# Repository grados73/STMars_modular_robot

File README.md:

# STMars Modular Robot
>My version of popular SMARS project, but THIS is distinguished by the fact that it is on STM32F411.

## Table of contents
* [General info](#general-info)
* [Screenshots](#screenshots)
* [Technologies](#technologies)
* [Features](#features)
* [Status](#status)
* [Inspiration](#inspiration)
* [Contact](#contact)

## General info
It is educational SMARS project based on STM32 BlackPill. I created this project to learn how to develop projects on STM32 and how to use my own 3D Printer.

STMars has two modes of working, the first one is remote control via Bluetooth, using a phone and HC-05 module, second mode is the ability to drive autonomously and to avoid obstacles.

## Screenshots

## Technologies
C,
HAL for STM32F4
Low-Layer drivers

STM32CubeIDE,
RoboRemo

## Code Examples

## Features
UART in DMA mode,
State machine.

## To-do list
Upgrade standalone mode.
Add calibration of engine speed by optocoupler

## Status
Project is in progress and i will develop them to learn ARM and STM32.

## Inspiration
It will be added.

## Contact
Created by https://www.linkedin.com/in/kamil-gradowski-8706991aa - feel free to contact me!
grados73

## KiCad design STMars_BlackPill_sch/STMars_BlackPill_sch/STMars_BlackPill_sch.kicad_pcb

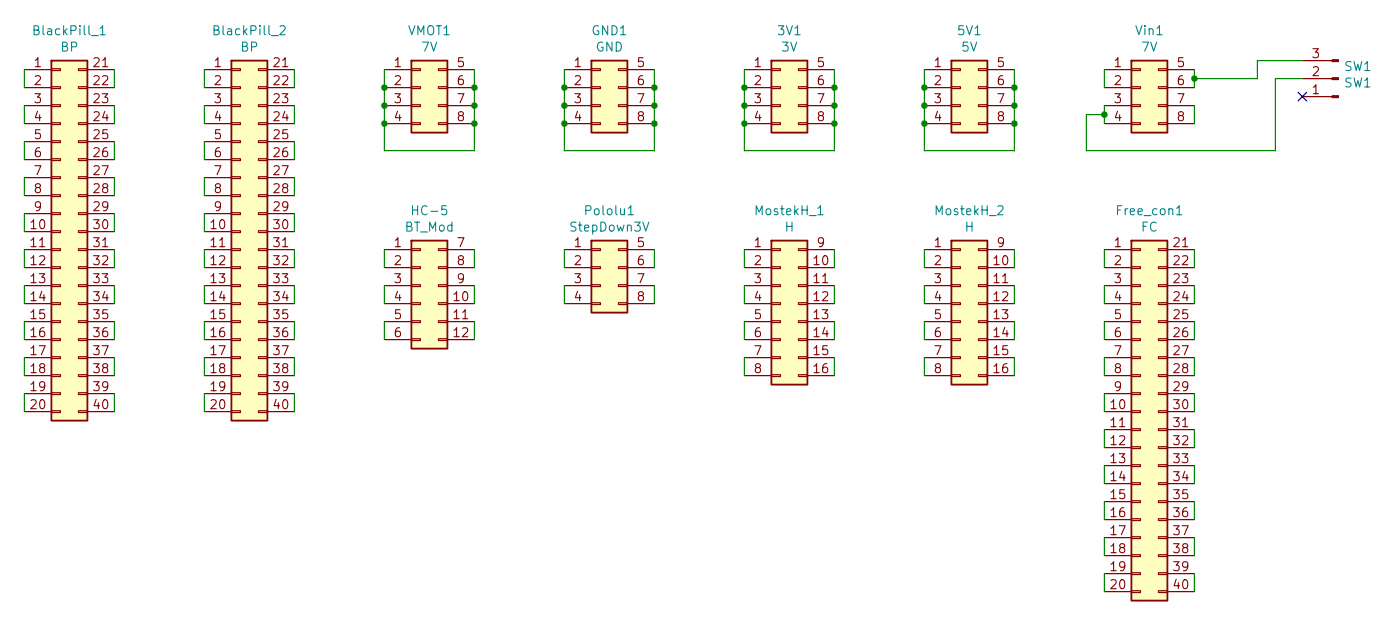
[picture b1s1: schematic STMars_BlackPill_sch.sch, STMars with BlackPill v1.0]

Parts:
3V1: 3V; PinHeader_2x04_P2.54mm_Vertical
5V1: 5V; PinHeader_2x04_P2.54mm_Vertical
BlackPill_1, BlackPill_2: BP; PinHeader_2x20_P2.54mm_Vertical
Free_con1: FC; PinHeader_2x20_P2.54mm_Vertical
GND1: GND; PinHeader_2x04_P2.54mm_Vertical
HC-5: BT_Mod; PinHeader_2x06_P2.54mm_Vertical
MostekH_1, MostekH_2: H; PinHeader_2x08_P2.54mm_Vertical
Pololu1: StepDown3V; PinHeader_2x04_P2.54mm_Vertical
SW1: SW1; PinHeader_1x03_P2.54mm_Vertical
VMOT1: 7V; PinHeader_2x04_P2.54mm_Vertical
Vin1: 7V; PinHeader_2x04_P2.54mm_Vertical

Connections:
unnamed: 3V1.1, 3V1.2, 3V1.3, 3V1.4, 3V1.5, 3V1.6, 3V1.7, 3V1.8
unnamed: 5V1.1, 5V1.2, 5V1.3, 5V1.4, 5V1.5, 5V1.6, 5V1.7, 5V1.8
unnamed: BlackPill_1.1, BlackPill_1.2
unnamed: BlackPill_1.3, BlackPill_1.4
unnamed: BlackPill_1.5, BlackPill_1.6
unnamed: BlackPill_1.7, BlackPill_1.8
unnamed: BlackPill_1.9, BlackPill_1.10
unnamed: BlackPill_1.11, BlackPill_1.12
unnamed: BlackPill_1.13, BlackPill_1.14
unnamed: BlackPill_1.15, BlackPill_1.16
unnamed: BlackPill_1.17, BlackPill_1.18
unnamed: BlackPill_1.19, BlackPill_1.20
unnamed: BlackPill_1.21, BlackPill_1.22
unnamed: BlackPill_1.23, BlackPill_1.24
unnamed: BlackPill_1.25, BlackPill_1.26
unnamed: BlackPill_1.27, BlackPill_1.28
unnamed: BlackPill_1.29, BlackPill_1.30
unnamed: BlackPill_1.31, BlackPill_1.32
unnamed: BlackPill_1.33, BlackPill_1.34
unnamed: BlackPill_1.35, BlackPill_1.36
unnamed: BlackPill_1.37, BlackPill_1.38
unnamed: BlackPill_1.39, BlackPill_1.40
unnamed: BlackPill_2.1, BlackPill_2.2
unnamed: BlackPill_2.3, BlackPill_2.4
unnamed: BlackPill_2.5, BlackPill_2.6
unnamed: BlackPill_2.7, BlackPill_2.8
unnamed: BlackPill_2.9, BlackPill_2.10
unnamed: BlackPill_2.11, BlackPill_2.12
unnamed: BlackPill_2.13, BlackPill_2.14
unnamed: BlackPill_2.15, BlackPill_2.16
unnamed: BlackPill_2.17, BlackPill_2.18
unnamed: BlackPill_2.19, BlackPill_2.20
unnamed: BlackPill_2.21, BlackPill_2.22
unnamed: BlackPill_2.23, BlackPill_2.24
unnamed: BlackPill_2.25, BlackPill_2.26
unnamed: BlackPill_2.27, BlackPill_2.28
unnamed: BlackPill_2.29, BlackPill_2.30
unnamed: BlackPill_2.31, BlackPill_2.32
unnamed: BlackPill_2.33, BlackPill_2.34
unnamed: BlackPill_2.35, BlackPill_2.36
unnamed: BlackPill_2.37, BlackPill_2.38
unnamed: BlackPill_2.39, BlackPill_2.40
unnamed: Free_con1.1, Free_con1.2
unnamed: Free_con1.3, Free_con1.4
unnamed: Free_con1.5, Free_con1.6
unnamed: Free_con1.7, Free_con1.8
unnamed: Free_con1.9, Free_con1.10
unnamed: Free_con1.11, Free_con1.12
unnamed: Free_con1.13, Free_con1.14
unnamed: Free_con1.15, Free_con1.16
unnamed: Free_con1.17, Free_con1.18
unnamed: Free_con1.19, Free_con1.20
unnamed: Free_con1.21, Free_con1.22
unnamed: Free_con1.23, Free_con1.24
unnamed: Free_con1.25, Free_con1.26
unnamed: Free_con1.27, Free_con1.28
unnamed: Free_con1.29, Free_con1.30
unnamed: Free_con1.31, Free_con1.32
unnamed: Free_con1.33, Free_con1.34
unnamed: Free_con1.35, Free_con1.36
unnamed: Free_con1.37, Free_con1.38
unnamed: Free_con1.39, Free_con1.40
unnamed: GND1.1, GND1.2, GND1.3, GND1.4, GND1.5, GND1.6, GND1.7, GND1.8
unnamed: HC-5.1, HC-5.2
unnamed: HC-5.3, HC-5.4
unnamed: HC-5.5, HC-5.6
unnamed: HC-5.7, HC-5.8
unnamed: HC-5.9, HC-5.10
unnamed: HC-5.11, HC-5.12
unnamed: MostekH_1.1, MostekH_1.2
unnamed: MostekH_1.3, MostekH_1.4
unnamed: MostekH_1.5, MostekH_1.6
unnamed: MostekH_1.7, MostekH_1.8
unnamed: MostekH_1.9, MostekH_1.10
unnamed: MostekH_1.11, MostekH_1.12
unnamed: MostekH_1.13, MostekH_1.14
unnamed: MostekH_1.15, MostekH_1.16
unnamed: MostekH_2.1, MostekH_2.2
unnamed: MostekH_2.3, MostekH_2.4
unnamed: MostekH_2.5, MostekH_2.6
unnamed: MostekH_2.7, MostekH_2.8
unnamed: MostekH_2.9, MostekH_2.10
unnamed: MostekH_2.11, MostekH_2.12
unnamed: MostekH_2.13, MostekH_2.14
unnamed: MostekH_2.15, MostekH_2.16
unnamed: Pololu1.1, Pololu1.2
unnamed: Pololu1.3, Pololu1.4
unnamed: Pololu1.5, Pololu1.6
unnamed: Pololu1.7, Pololu1.8
unnamed: SW1.2, Vin1.3, Vin1.4
unnamed: SW1.3, Vin1.5, Vin1.6
unnamed: VMOT1.1, VMOT1.2, VMOT1.3, VMOT1.4, VMOT1.5, VMOT1.6, VMOT1.7, VMOT1.8
unnamed: Vin1.1, Vin1.2
unnamed: Vin1.7, Vin1.8

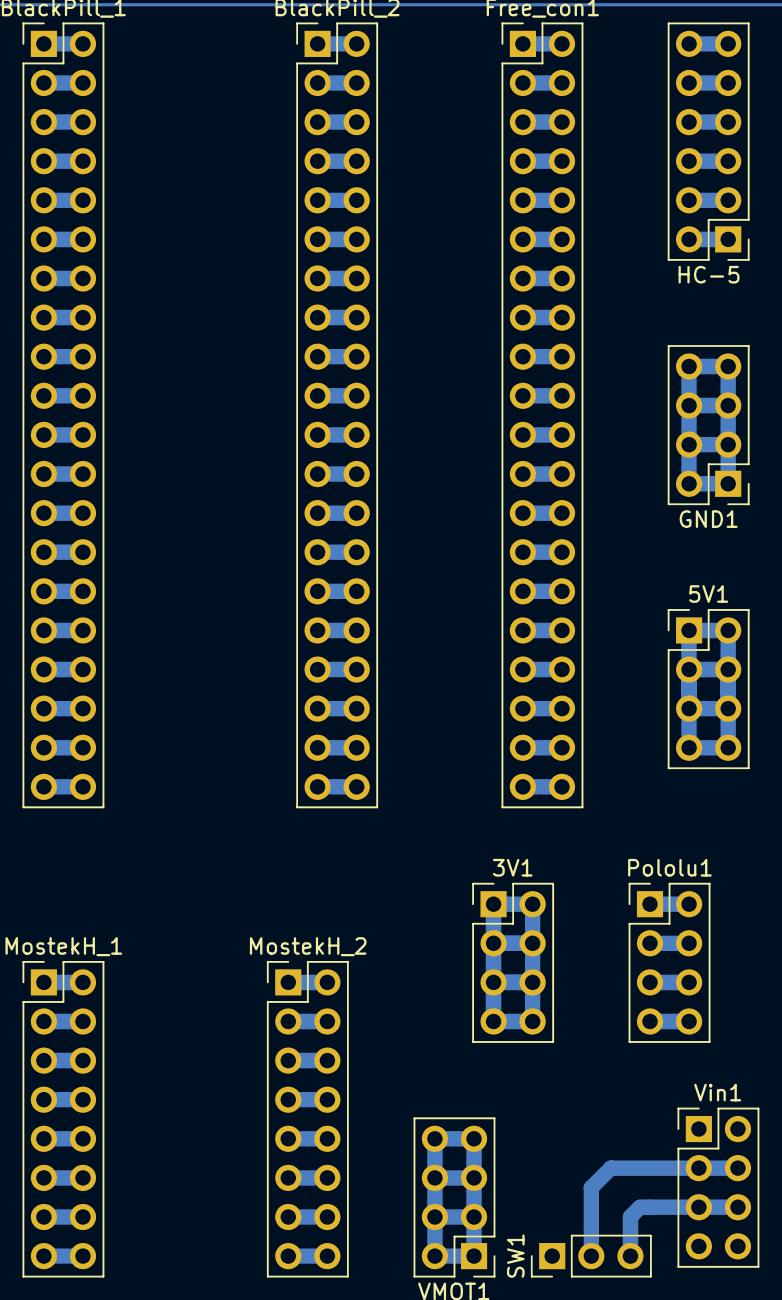
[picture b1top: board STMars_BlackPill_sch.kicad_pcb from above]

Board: 2 copper layers, 13 parts (0 on the bottom side), 94 nets.

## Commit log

2021-01-29 first commit -empty project
2021-01-29 Delate metadane - unused directory
    added by mistake
2021-01-29 UART Postawiony na DMA, ale coś w rejestrze się wykrzacza
2021-01-29 wersja z uartem w IT
2021-01-29 Dane przechodza do DMA_RX_Buffer, ale nie ma ich w UART_Rx_buffer
2021-02-02 First version of board
2021-02-02 Dziala caly parsing LED, dziala parsing MOTOR, trzeba napisac funckje obslugi ruchu w motion.c
2021-02-02 Added first version od README
2021-02-03 dodana pusta maszyna stanow
2021-02-03 dodane puste funkcje do obslugi maszyny stanow
2021-02-03 dodane dwa nowe timery PWM oraz 4 GPIO Output do sterownaia mostkiem H
2021-02-09 Photo of STMars during the first ride.
2021-02-09 dodany folder z pierwszym foto
2021-02-09 Aktualizacja o zdjęcie i poprawiony opis.
2021-02-10 Dodana obsluga maszyny stanow
2021-02-10 Poprawione funkcje cofania w sterowaniu silnikami
2021-02-12 zbilansowane silniki ręcznie
2021-02-12 wywalona słaba funkcja liczenia czasu z HAL_Gettick(); i obsluga silnikow zrobiona na przerwaniu normalnym
2021-02-12 Dodane liczenie odleglosci do przeszkody z HC-SR04 w Input Capture TIM1 Mode
2021-02-12 dodany prototyp funkcji jazdy autonomicznej i obsluga parsowania tego trybu
2021-02-12 dodana mozliwosc jazdy autonomicznej + informacja zwrotna o wybranym trybie jazdy
2021-02-16 Add photo with RoboRemo Api
2021-02-16 Add code examples
